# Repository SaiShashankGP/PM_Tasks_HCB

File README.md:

# PM_Tasks_HCB

All my task files can be found here

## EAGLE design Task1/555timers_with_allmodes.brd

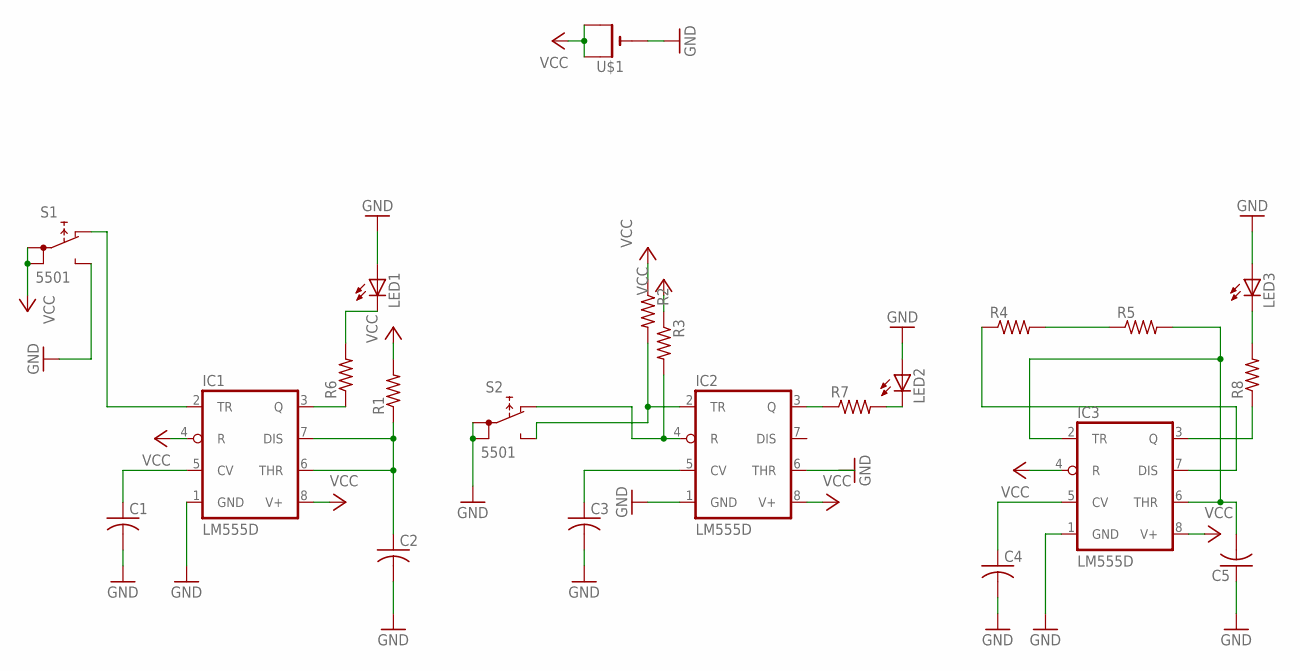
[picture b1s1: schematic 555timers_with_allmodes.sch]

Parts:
C1, C2, C3, C4, C5: C-USC0805; C0805
IC1, IC2, IC3: LM555D; SO08
LED1, LED2, LED3: LEDCHIPLED_0805; CHIPLED_0805
R1, R2, R3, R4, R5, R6, R7, R8: R-US_FLIPFLOP; 0805-THM
S1, S2: 5501
U$1: CR1220SMT; CR1220-SMD

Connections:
GND: C1.2, C2.2, C3.2, C4.2, C5.1, IC1.1 (GND), IC2.1 (GND), IC2.6 (THR), IC3.1 (GND), LED1.A, LED2.A, LED3.A, S1.NO, S2.1A, S2.1B, U$1.-
unnamed: C1.1, IC1.5 (CV)
unnamed: IC2.2 (TR), R2.2, S2.NO
unnamed: C2.1, IC1.6 (THR), IC1.7 (DIS), R1.1
unnamed: IC1.2 (TR), S1.NC
unnamed: LED1.C, R6.2
unnamed: C3.1, IC2.5 (CV)
unnamed: IC2.4 (R), R3.2, S2.NC
unnamed: C4.1, IC3.5 (CV)
unnamed: IC2.3 (Q), R7.1
unnamed: C5.2, IC3.2 (TR), IC3.6 (THR), R5.2
unnamed: R4.2, R5.1
unnamed: IC1.3 (Q), R6.1
unnamed: IC3.7 (DIS), R4.1
unnamed: IC3.3 (Q), R8.1
unnamed: LED2.C, R7.2
unnamed: LED3.C, R8.2
VCC: IC1.4 (R), IC1.8 (V+), IC2.8 (V+), IC3.4 (R), IC3.8 (V+), R1.2, R2.1, R3.1, S1.1A, S1.1B, U$1.+$1 (+), U$1.+$2 (+1)

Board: 2 copper layers, 22 parts (0 on the bottom side), 18 nets, no tracks yet.

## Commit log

2021-06-03 This is just a test
2021-06-03 created Task1 and Task1/test.txt
2021-06-30 Knight Piece design uploaded
